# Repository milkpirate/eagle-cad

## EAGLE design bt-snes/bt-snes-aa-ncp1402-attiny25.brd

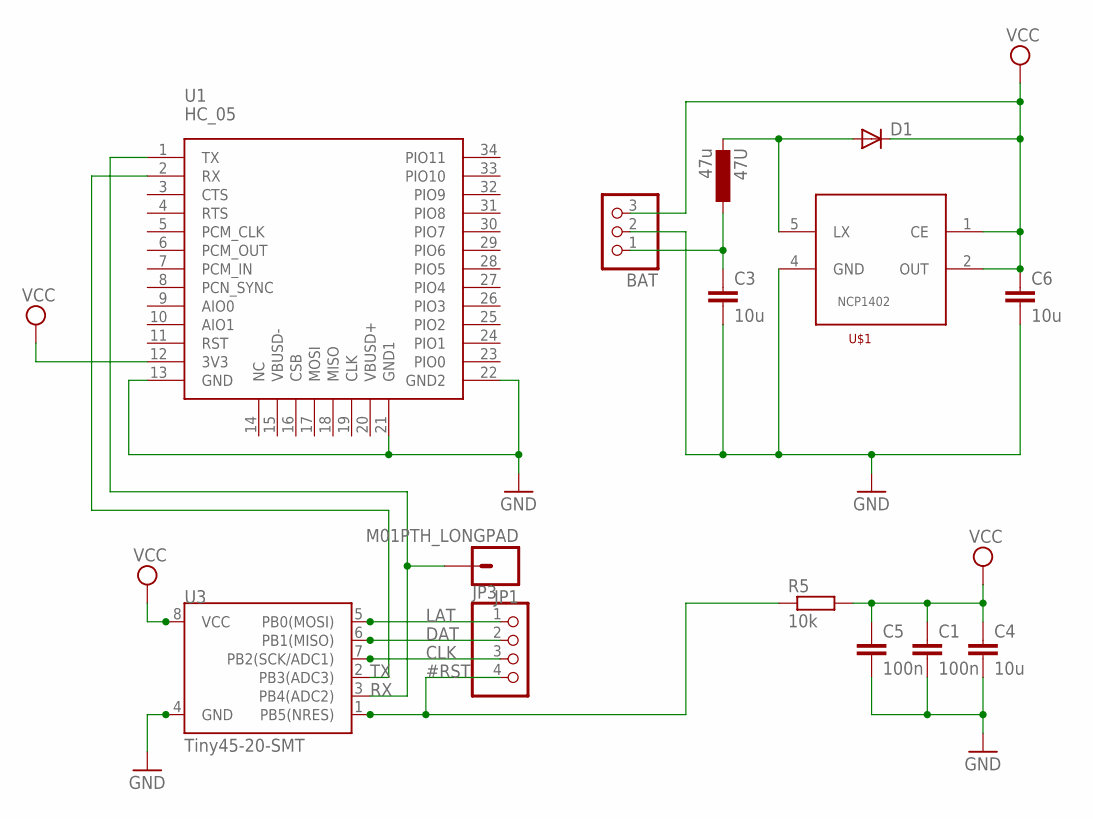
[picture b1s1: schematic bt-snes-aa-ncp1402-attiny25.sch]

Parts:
47U: 47u; C1210
BAT: PINHD-1X3; 1X03
C1, C5: 100n; C0805K
C3, C4, C6: 10u; C0805K
D1: DIODE-SOD80C; SOD80C
JP1: M01PTH_LONGPAD; 1X01_LONGPAD
JP3: PINHD-1X4; 1X04
R5: 10k; M0805
U1: HC_05; BLUETOOTH_SMD
U3: Tiny45-20-SMT; SO08-EIAJ
U$1: NCP1402; SOT23-5

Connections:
#RST: JP3.4, R5.1, U3.1 (PB5(NRES))
CLK: JP3.3, U3.7 (PB2(SCK/ADC1))
DAT: JP3.2, U3.6 (PB1(MISO))
GND: BAT.2, C1.2, C3.2, C4.2, C5.2, C6.2, U1.13 (GND), U1.21 (GND1), U1.22 (GND2), U3.4 (GND), U$1.4 (GND)
LAT: JP3.1, U3.5 (PB0(MOSI))
unnamed: 47U.1, BAT.1, C3.1
unnamed: 47U.2, D1.A, U$1.5 (LX)
RX: JP1.1, U1.1 (TX), U3.3 (PB4(ADC2))
TX: U1.2 (RX), U3.2 (PB3(ADC3))
VCC: BAT.3, C1.1, C4.1, C5.1, C6.1, D1.C, R5.2, U1.12 (3V3), U3.8 (VCC), U$1.1 (CE), U$1.2 (OUT)

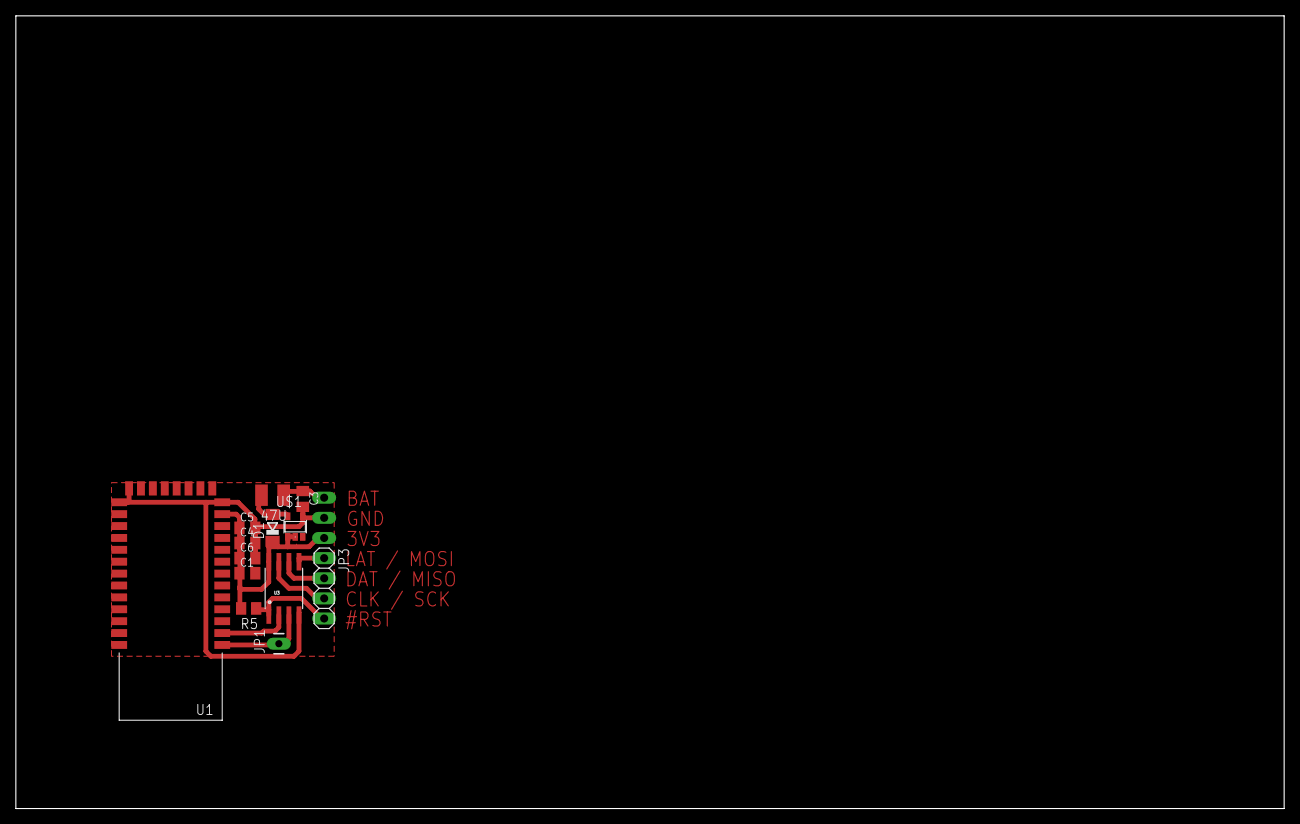
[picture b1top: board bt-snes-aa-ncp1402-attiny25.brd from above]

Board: 2 copper layers, 160.0 x 100.0 mm, 14 parts (1 on the bottom side), 10 nets.

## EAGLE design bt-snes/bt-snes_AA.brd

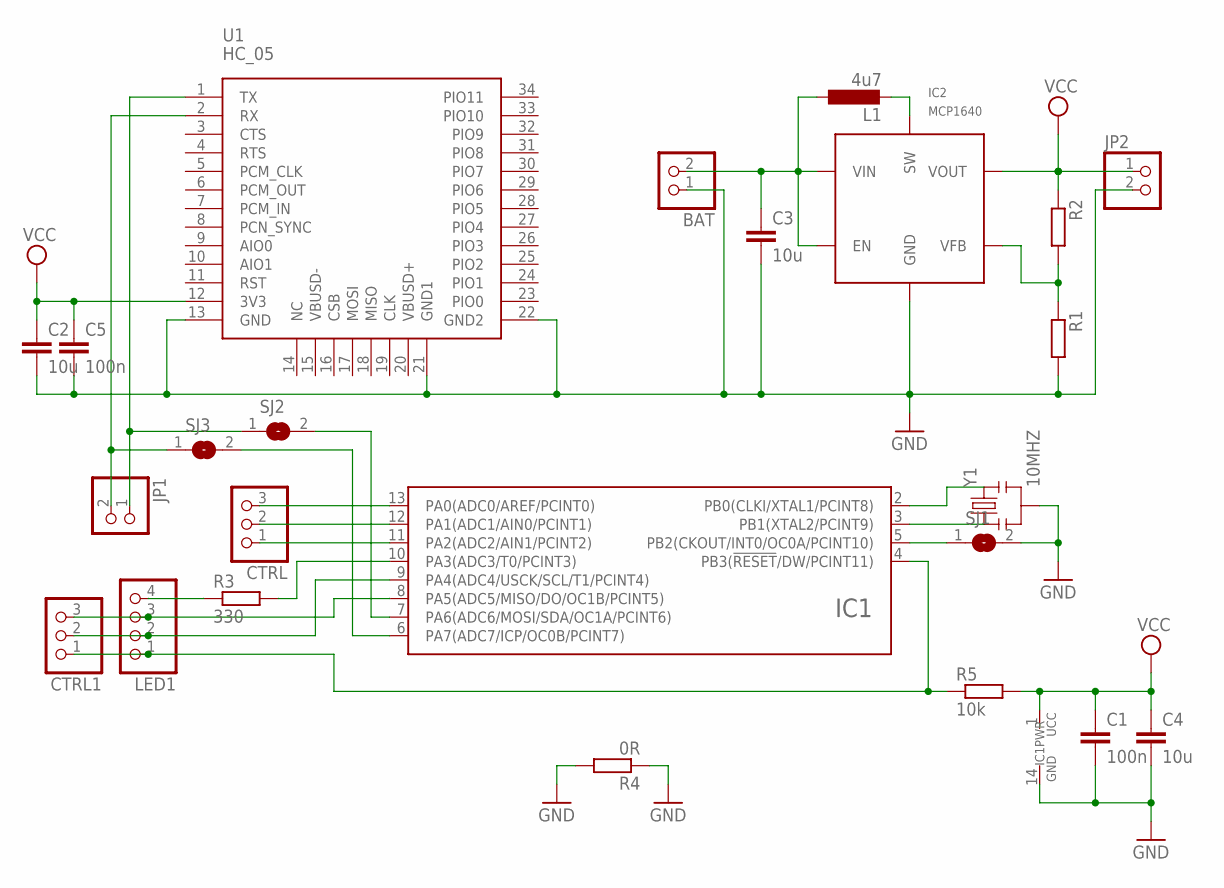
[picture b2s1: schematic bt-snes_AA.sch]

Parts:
BAT: PINHD-1X2; 1X02
C1, C5: 100n; C0805K
C2, C3, C4: 10u; C0805K
CTRL, CTRL1: PINHD-1X3; 1X03
IC1: ATTINY24/44/84-SSU; SOIC14
IC2: MCP1640; SOT23-6
JP1, JP2: PINHD-1X2; 1X02
L1: 4u7; C1210
LED1: PINHD-1X4; 1X04
R1, R2: R-EU_M0805; M0805
R3: 330; M0805
R4: 0R; R1206W
R5: 10k; M0805
SJ1, SJ2, SJ3: SJ
U1: HC_05; BLUETOOTH_SMD
Y1: 10MHZ; RESONATOR-SMD

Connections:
GND: BAT.1, C1.2, C2.2, C3.2, C4.2, C5.2, IC1.14 (GND), IC2.2 (GND), JP2.2, R1.2, R4.1, R4.2, SJ1.2, U1.13 (GND), U1.21 (GND1), U1.22 (GND2), Y1.2
unnamed: IC1.3 (PB1(XTAL2/PCINT9)), Y1.1
unnamed: IC1.2 (PB0(CLKI/XTAL1/PCINT8)), Y1.3
unnamed: JP1.1, SJ2.1, U1.1 (TX)
unnamed: CTRL.1, IC1.11 (PA2(ADC2/AIN1/PCINT2))
unnamed: JP1.2, SJ3.1, U1.2 (RX)
unnamed: CTRL1.3, IC1.8 (PA5(ADC5/MISO/DO/OC1B/PCINT5)), LED1.3
unnamed: CTRL.2, IC1.12 (PA1(ADC1/AIN0/PCINT1))
unnamed: CTRL.3, IC1.13 (PA0(ADC0/AREF/PCINT0))
unnamed: CTRL1.2, IC1.9 (PA4(ADC4/USCK/SCL/T1/PCINT4)), LED1.2
unnamed: IC1.7 (PA6(ADC6/MOSI/SDA/OC1A/PCINT6)), SJ2.2
unnamed: IC1.6 (PA7(ADC7/ICP/OC0B/PCINT7)), SJ3.2
unnamed: IC1.5 (PB2(CKOUT/INT0/OC0A/PCINT10)), SJ1.1
unnamed: BAT.2, C3.1, IC2.3 (EN), IC2.6 (VIN), L1.1
unnamed: IC2.4 (VFB), R1.1, R2.2
unnamed: LED1.4, R3.1
unnamed: IC2.1 (SW), L1.2
unnamed: CTRL1.1, IC1.4 (PB3(!RESET!/DW/PCINT11)), LED1.1, R5.1
unnamed: IC1.10 (PA3(ADC3/T0/PCINT3)), R3.2
VCC: C1.1, C2.1, C4.1, C5.1, IC1.1 (UCC), IC2.5 (VOUT), JP2.1, R2.1, R5.2, U1.12 (3V3)

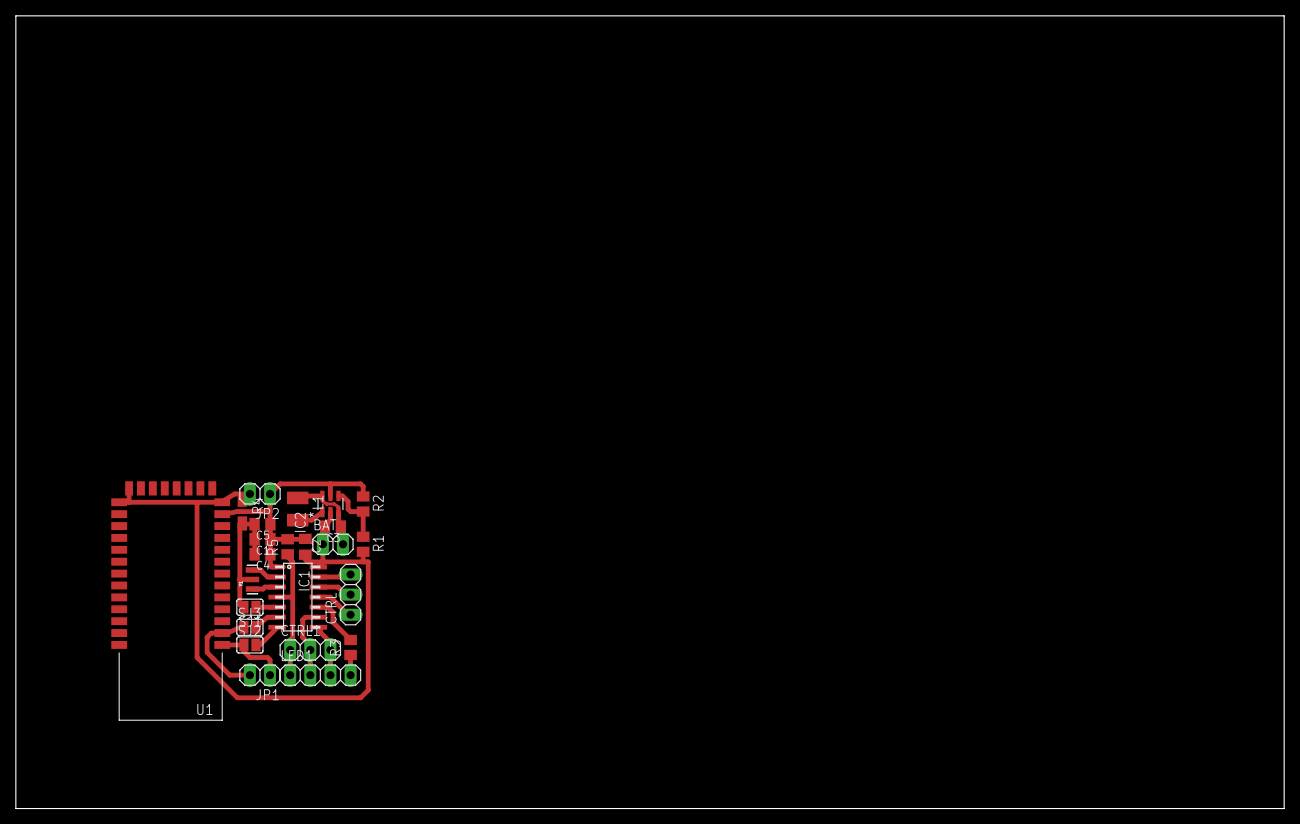
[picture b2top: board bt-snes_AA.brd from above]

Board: 2 copper layers, 160.0 x 100.0 mm, 24 parts (0 on the bottom side), 20 nets.

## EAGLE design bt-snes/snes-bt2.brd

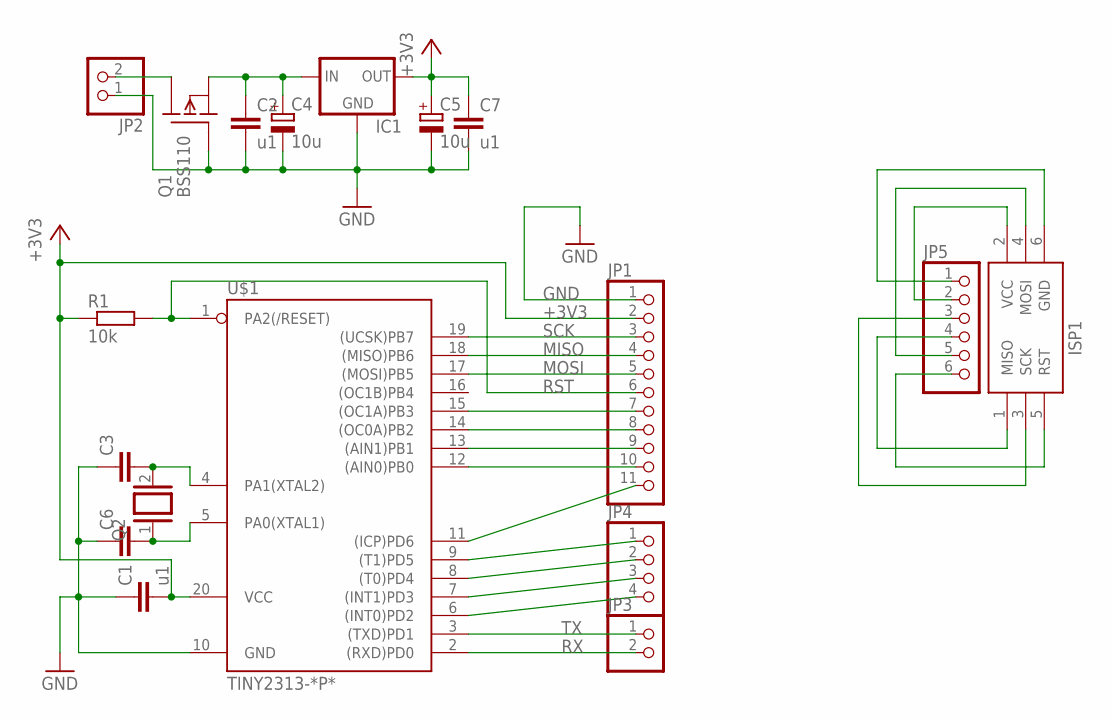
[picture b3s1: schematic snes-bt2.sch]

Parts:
C1, C2, C7: u1; C025-025X050
C3, C6: C-EUC0805K; C0805K
C4, C5: 10u; E2,5-6E
IC1: MCP1700_TO92-THIN; TO-92
ISP1: AVRISP-6; AVRISP
JP1: PINHD-1X11; 1X11
JP2, JP3: PINHD-1X2; 1X02
JP4: PINHD-1X4; 1X04
JP5: PINHD-1X6; 1X06
Q1: BSS110; TO92
Q2: XTAL/S; QS
R1: 10k; 0204/7
U$1: TINY2313-*P*; DIL20

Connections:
+3V3: C1.2, C5.+, C7.1, IC1.3 (OUT), JP1.2, R1.1, U$1.20 (VCC)
GND: C1.1, C2.2, C3.1, C4.-, C5.-, C6.1, C7.2, IC1.1 (GND), JP1.1, JP2.1, Q1.2 (G), U$1.10 (GND)
ISP_GND: ISP1.6 (GND), JP5.1
MISO: JP1.4, U$1.18 ((MISO)PB6)
MOSI: JP1.5, U$1.17 ((MOSI)PB5)
unnamed: C6.2, Q2.1, U$1.5 (PA0(XTAL1))
unnamed: C3.2, Q2.2, U$1.4 (PA1(XTAL2))
unnamed: JP1.11, U$1.11 ((ICP)PD6)
unnamed: ISP1.2 (VCC), JP5.2
unnamed: C2.1, C4.+, IC1.2 (IN), Q1.1 (S)
unnamed: JP2.2, Q1.3 (D)
unnamed: ISP1.4 (MOSI), JP5.5
unnamed: ISP1.1 (MISO), JP5.4
unnamed: ISP1.5 (RST), JP5.6
unnamed: ISP1.3 (SCK), JP5.3
unnamed: JP1.7, U$1.15 ((OC1A)PB3)
unnamed: JP1.8, U$1.14 ((OC0A)PB2)
unnamed: JP1.9, U$1.13 ((AIN1)PB1)
unnamed: JP1.10, U$1.12 ((AIN0)PB0)
unnamed: JP4.1, U$1.9 ((T1)PD5)
unnamed: JP4.2, U$1.8 ((T0)PD4)
unnamed: JP4.3, U$1.7 ((INT1)PD3)
unnamed: JP4.4, U$1.6 ((INT0)PD2)
RST: JP1.6, R1.2, U$1.1 (PA2(/RESET))
RX: JP3.2, U$1.2 ((RXD)PD0)
SCK: JP1.3, U$1.19 ((UCSK)PB7)
TX: JP3.1, U$1.3 ((TXD)PD1)

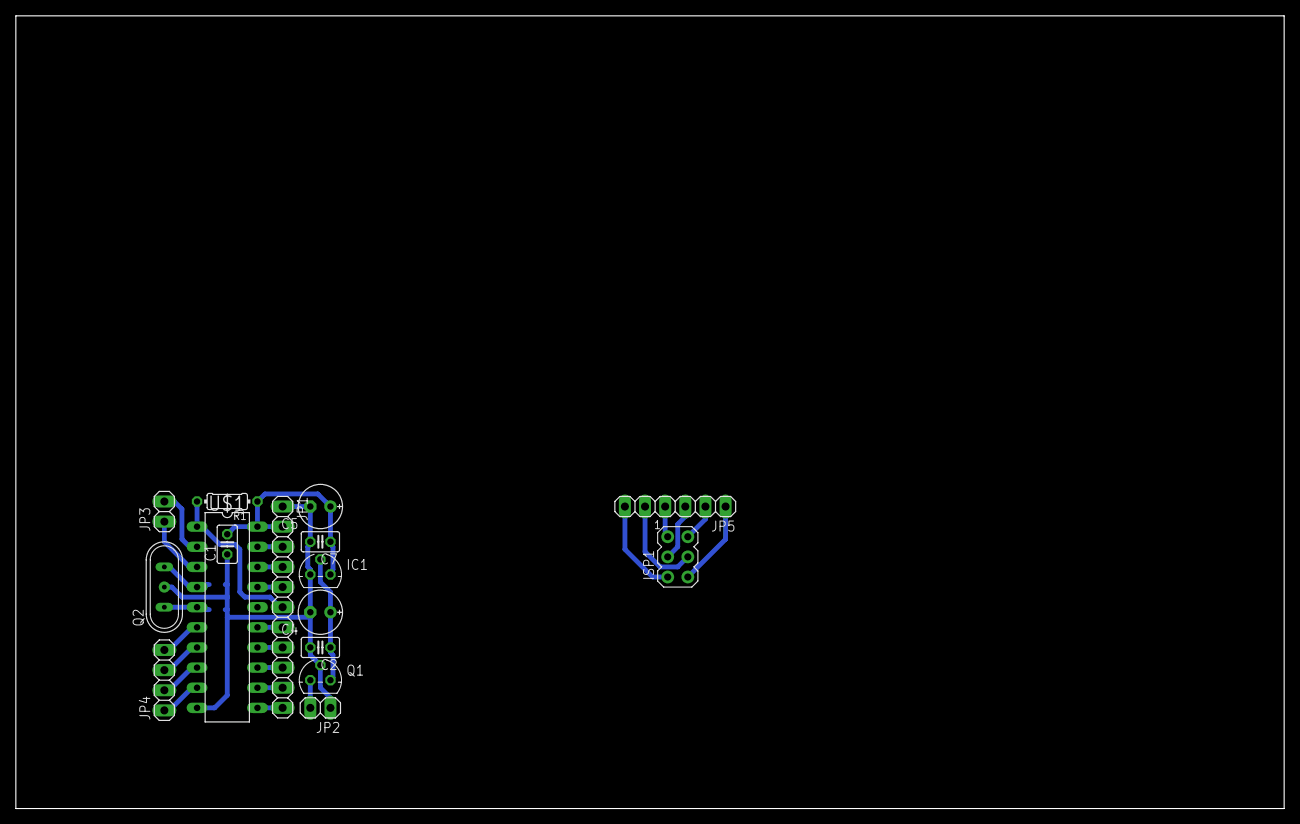
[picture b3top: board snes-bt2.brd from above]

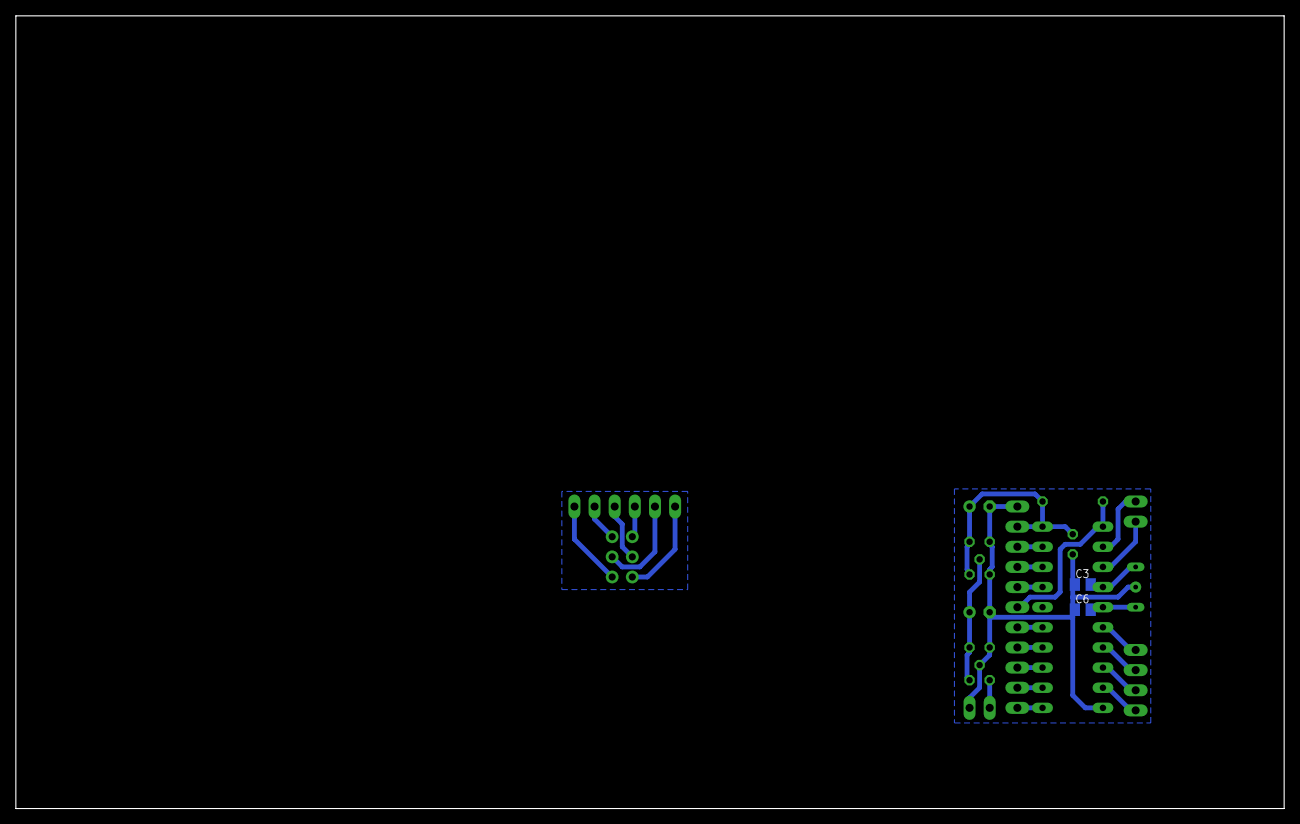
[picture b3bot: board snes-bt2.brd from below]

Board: 2 copper layers, 160.0 x 100.0 mm, 18 parts (2 on the bottom side), 27 nets.

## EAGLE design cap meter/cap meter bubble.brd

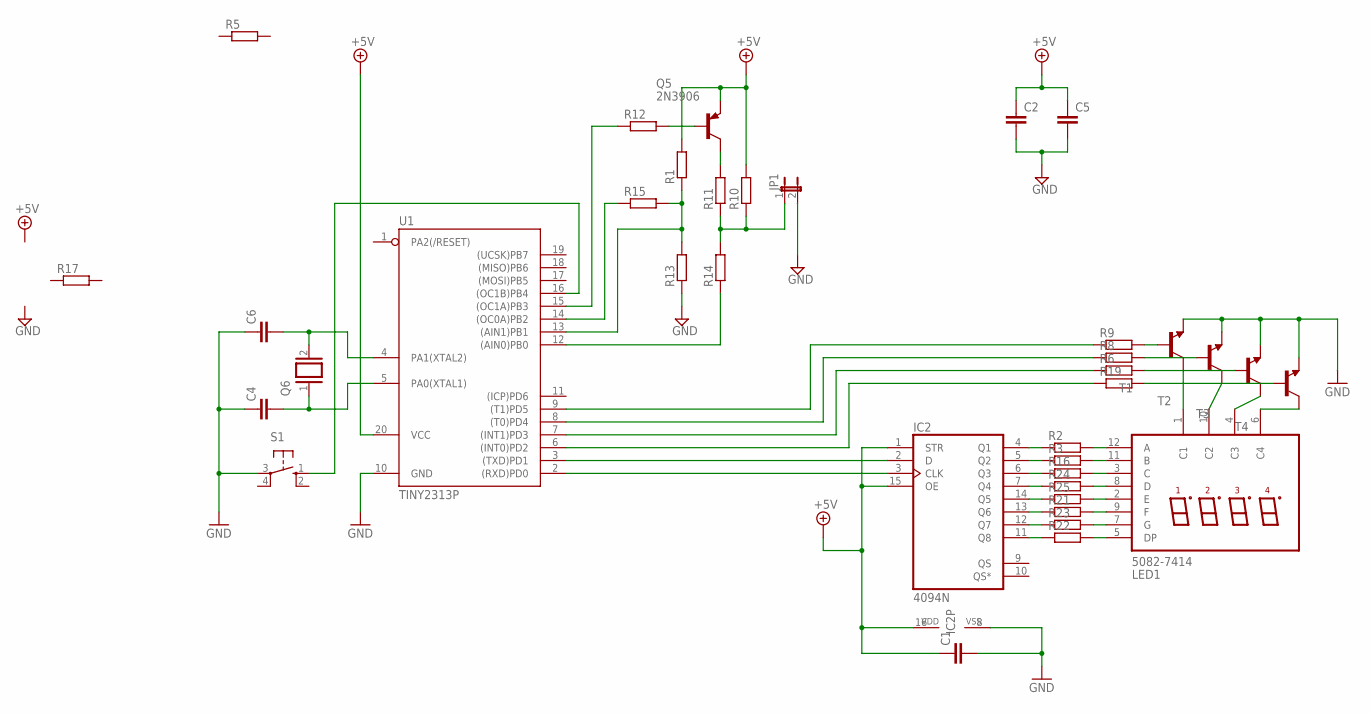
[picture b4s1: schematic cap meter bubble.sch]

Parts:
C1, C2, C4, C5, C6: C-EU025-025X050; C025-025X050
IC2: 4094N; DIL16
JP1: JP1E; JP1
LED1: 5082-7414
Q5: 2N3906; TO92
Q6: XTAL/S; QS
R1, R5, R10, R11, R12, R13, R14, R15, R17: R-EU_0204/2V; 0204V
R2, R3, R6, R8, R9, R16, R19, R21, R22, R23, R24, R25: R-EU_0204/7; 0204/7
S1: 10-XX; B3F-10XX
T1, T2, T3, T4: -NPN-TO92-EBC; TO92-EBC
U1: TINY2313P; DIL20

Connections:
+5V: C1.1, C2.1, C5.1, IC2.1 (STR), IC2.15 (OE), IC2.16 (VDD), Q5.3 (E), R1.2, R10.2
GND: C1.2, C2.2, C4.1, C5.2, C6.1, IC2.8 (VSS), JP1.2, R13.1, S1.3, T1.E, T2.E, T3.E, T4.E, U1.10 (GND)
unnamed: LED1.12 (A), R2.2
unnamed: C4.2, Q6.1
unnamed: C6.2, Q6.2
unnamed: S1.1 (S), U1.16 ((OC1B)PB4)
unnamed: LED1.11 (B), R3.2
unnamed: Q5.1 (C), R11.2
unnamed: JP1.1, R10.1, R11.1, R14.2
unnamed: R1.1, R13.2, R15.2, U1.13 ((AIN1)PB1)
unnamed: Q5.2 (B), R12.2
unnamed: R12.1, U1.15 ((OC1A)PB3)
unnamed: R15.1, U1.14 ((OC0A)PB2)
unnamed: R14.1, U1.12 ((AIN0)PB0)
unnamed: IC2.2 (D), U1.3 ((TXD)PD1)
unnamed: IC2.3 (CLK), U1.2 ((RXD)PD0)
unnamed: LED1.3 (C), R16.2
unnamed: IC2.4 (Q1), R2.1
unnamed: IC2.5 (Q2), R3.1
unnamed: IC2.6 (Q3), R16.1
unnamed: IC2.7 (Q4), R24.1
unnamed: IC2.14 (Q5), R25.1
unnamed: IC2.13 (Q6), R21.1
unnamed: IC2.12 (Q7), R23.1
unnamed: IC2.11 (Q8), R22.1
unnamed: LED1.9 (F), R21.2
unnamed: LED1.5 (DP), R22.2
unnamed: LED1.7 (G), R23.2
unnamed: LED1.8 (D), R24.2
unnamed: LED1.2 (E), R25.2
unnamed: LED1.1 (C1), T1.C
unnamed: LED1.10 (C2), T2.C
unnamed: LED1.4 (C3), T3.C
unnamed: LED1.6 (C4), T4.C
unnamed: R9.2, T1.B
unnamed: R8.2, T2.B
unnamed: R19.1, U1.6 ((INT0)PD2)
unnamed: R6.1, U1.7 ((INT1)PD3)
unnamed: R8.1, U1.8 ((T0)PD4)
unnamed: R9.1, U1.9 ((T1)PD5)
unnamed: R6.2, T3.B
unnamed: R19.2, T4.B
VCC: U1.20 (VCC)

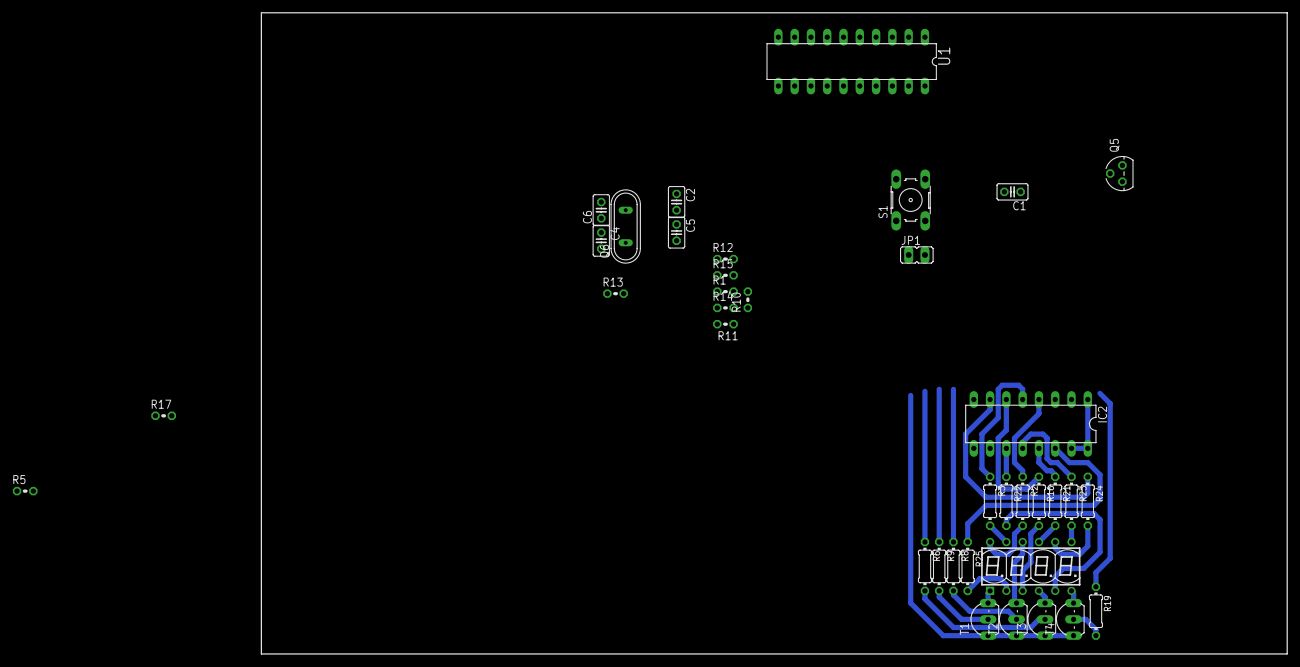
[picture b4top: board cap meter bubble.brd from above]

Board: 2 copper layers, 160.0 x 100.0 mm, 37 parts (0 on the bottom side), 42 nets.

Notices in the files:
parts and their libraries:
SparkFun-DigitalIC: Licensing: Creative Commons ShareAlike 4.0 International - https://creativecommons.org/licenses/by-sa/4.0
SparkFun-FreqCtrl: Licensing: CC v3.0 Share-Alike You are welcome to use this library for commercial purposes.
